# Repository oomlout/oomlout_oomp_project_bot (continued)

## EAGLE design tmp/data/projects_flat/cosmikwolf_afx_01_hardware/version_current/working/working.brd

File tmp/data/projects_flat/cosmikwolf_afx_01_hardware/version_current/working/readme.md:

# afx-01_hardware by cosmikwolf  
This is a harvested standardized copy of a project from github.  
The original project can be found at:  
https://github.com/cosmikwolf/afx-01_hardware  
Please consult that link for additional, details, files, and license information.  
Note: It was auto harvested and if the original repo had more than one board file or anything out of the ordinary the files here are likely not representative.

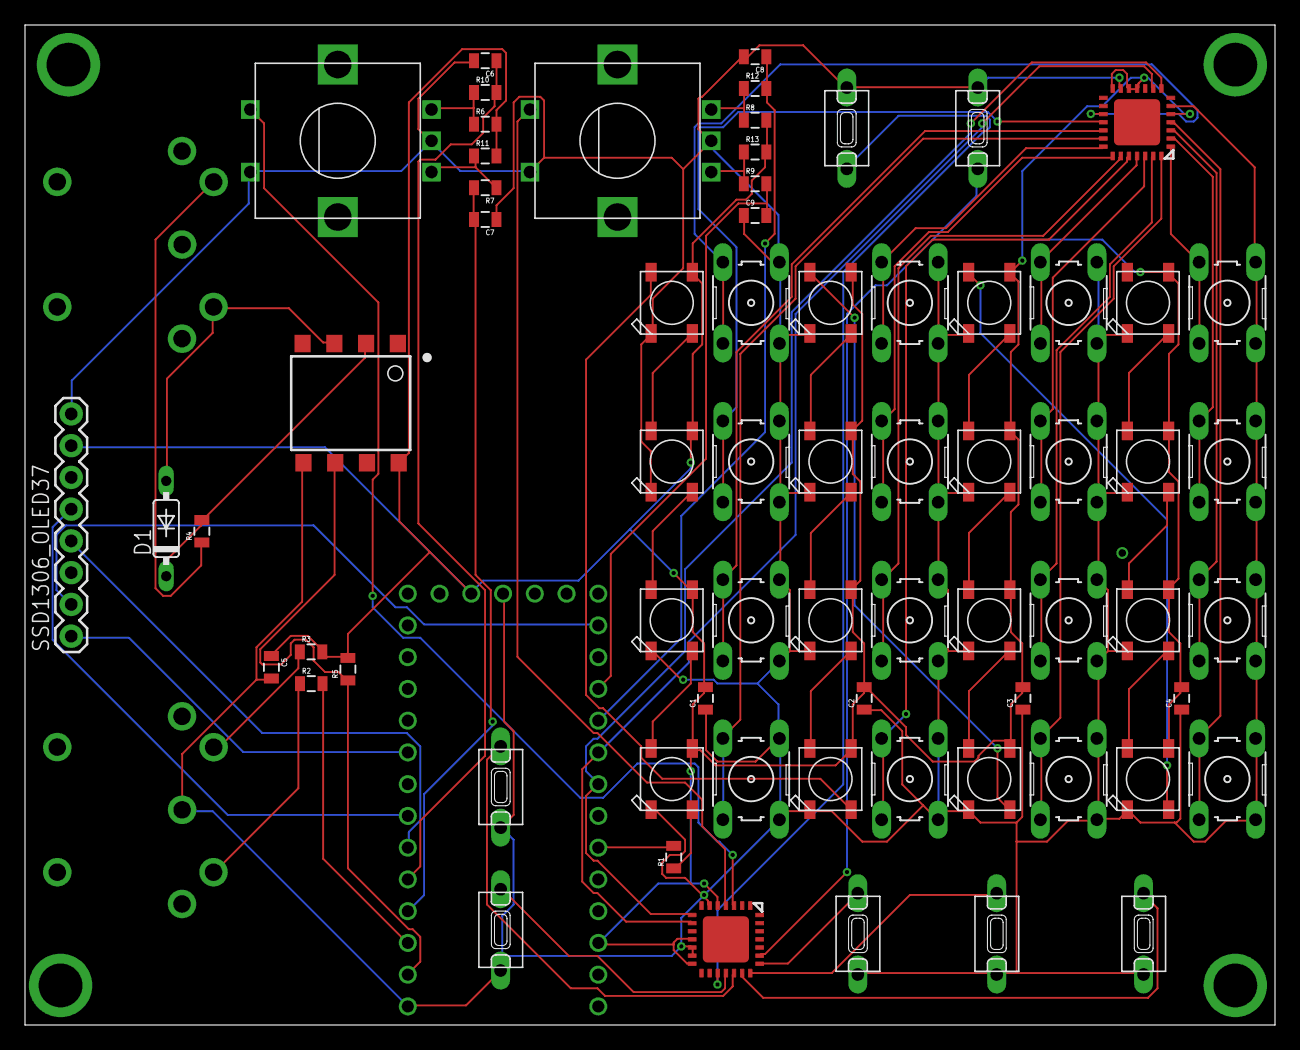
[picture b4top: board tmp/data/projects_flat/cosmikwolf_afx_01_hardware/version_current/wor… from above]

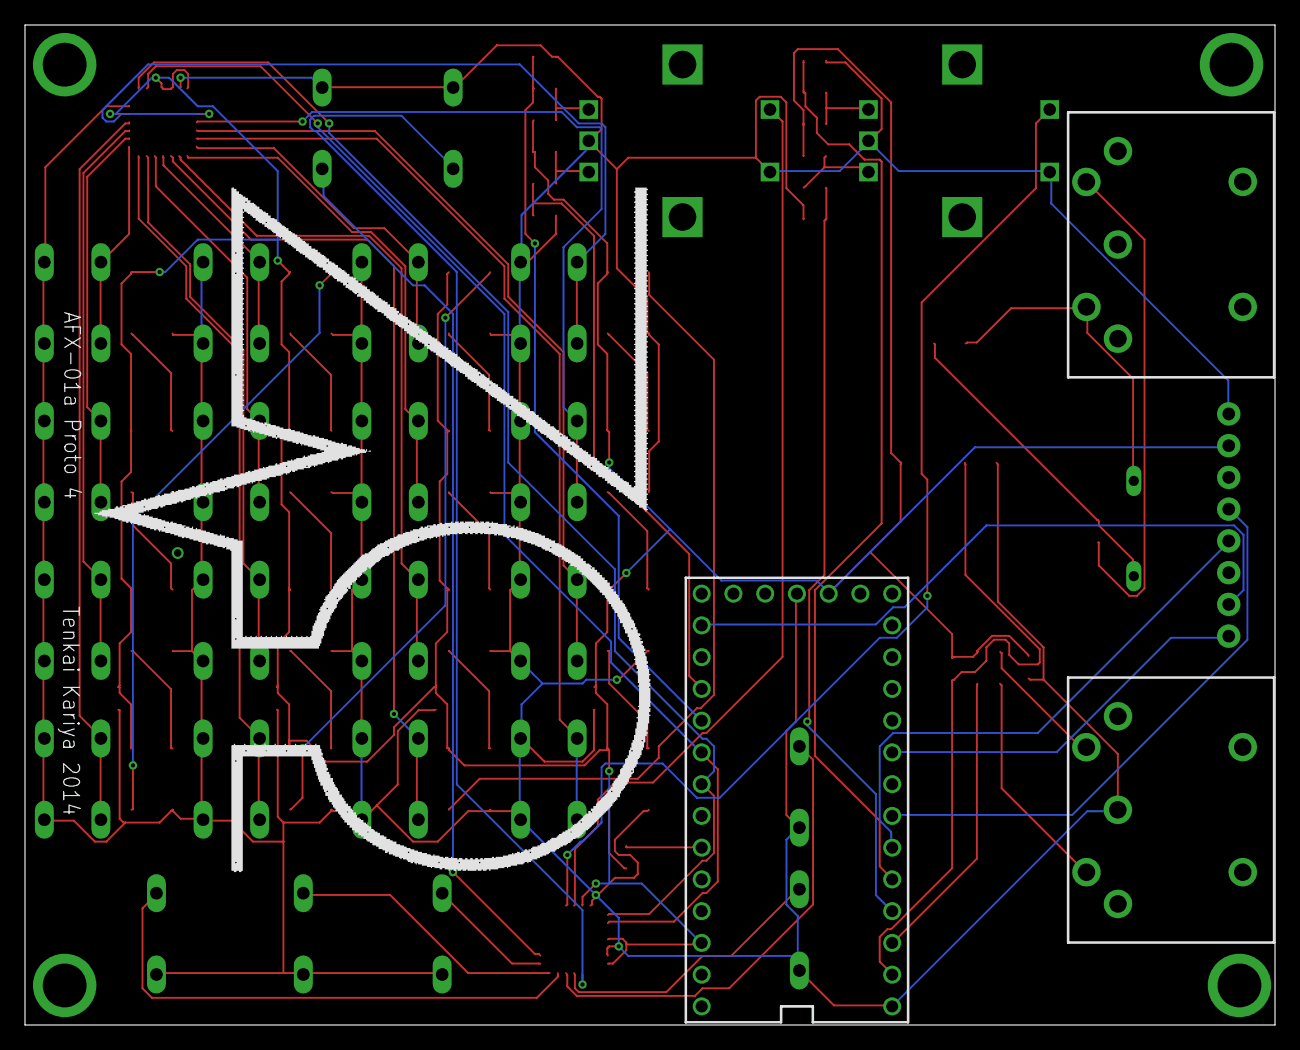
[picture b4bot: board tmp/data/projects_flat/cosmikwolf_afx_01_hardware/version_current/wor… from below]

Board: 2 copper layers, 100.0 x 80.0 mm, 71 parts (3 on the bottom side), 65 nets.

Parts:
C1, C2, C3, C4, C5: 100uF; 0805
C6, C7, C8, C9: 0.01uF; 0805
D1: 1N4148DO35-7; DO35-7
L1, L2, L3, L4, L5, L6, L7, L8, L9, L10, L11, L12, L13, L14, L15, L16: WS2812B
MCP0, MCP1: MCP23017ML; QFN28-ML_6X6MM
R1: 500; 0805
R2, R3, R4: 220; 0805
R5: 270; 0805
R6, R7, R8, R9, R10, R11, R12, R13: 10k; 0805
S1, S2, S3, S4, S5, S6, S7, S8, S9, S10, S11, S12, S13, S14, S15, S16: B3F-10XX
SS1, SS2, SS3, SS4, SS5, SS6, SS7: B3F-10XX
SSD1306_OLED37: 1X08_ROUND
SW1, SW2: EC12E_SW; ALPS_EC12E_SW
U1: 6N138M; 8-SMD
U$1: TEENSY_3.1_BASIC
U$2, U$3: MIDI_CONN_FEMALE_SUPPORT; DIN_5_FEMALE_SUPPORT

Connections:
GND: C1.1, C2.1, C3.1, C4.1, C5.2, C6.2, C7.1, C8.2, C9.1, L1.3-GND, L2.3-GND, L3.3-GND, L4.3-GND, L5.3-GND, L6.3-GND, L7.3-GND, L8.3-GND, L9.3-GND, L10.3-GND, L11.3-GND, L12.3-GND, L13.3-GND, L14.3-GND, L15.3-GND, L16.3-GND, MCP0.6, MCP0.13, MCP1.6, MCP1.12, MCP1.13, S1.3, S1.4, S2.3, S2.4, S3.3, S3.4, S4.3, S4.4, S5.3, S5.4, S6.3, S6.4, S7.3, S7.4, S8.3, S8.4, S9.3, S9.4, S10.3, S10.4, S11.3, S11.4, S12.3, S12.4, S13.3, S13.4, S14.3, S14.4, S15.3, S15.4, S16.3, S16.4, SS1.1, SS2.1, SS3.1, SS4.1, SS5.1, SS6.1, SS7.1, SSD1306_OLED37.8, SW1.C, SW1.D, SW2.C, SW2.D, U1.5, U$1.GND, U$1.GND1, U$2.2
unnamed: L1.2-DOUT, L2.4-DIN
unnamed: L2.2-DOUT, L3.4-DIN
unnamed: L3.2-DOUT, L4.4-DIN
unnamed: L5.2-DOUT, L6.4-DIN
unnamed: L6.2-DOUT, L7.4-DIN
unnamed: L7.2-DOUT, L8.4-DIN
unnamed: L9.2-DOUT, L10.4-DIN
unnamed: L10.2-DOUT, L11.4-DIN
unnamed: L11.2-DOUT, L12.4-DIN
unnamed: L13.2-DOUT, L14.4-DIN
unnamed: L14.2-DOUT, L15.4-DIN
unnamed: L15.2-DOUT, L16.4-DIN
unnamed: L4.2-DOUT, L5.4-DIN
unnamed: R2.1, U$2.5
unnamed: R2.2, U$1.1
unnamed: MCP0.20, S1.1, S1.2
unnamed: MCP0.19, S2.1, S2.2
unnamed: MCP0.18, S3.1, S3.2
unnamed: MCP0.17, S4.1, S4.2
unnamed: R1.2, U$1.21/A7
unnamed: MCP0.24, S5.1, S5.2
unnamed: MCP0.23, S6.1, S6.2
unnamed: MCP0.22, S7.1, S7.2
unnamed: MCP0.21, S8.1, S8.2
unnamed: MCP0.28, S9.1, S9.2
unnamed: MCP0.27, S10.1, S10.2
unnamed: MCP0.26, S11.1, S11.2
unnamed: MCP0.25, S12.1, S12.2
unnamed: MCP0.4, S13.1, S13.2
unnamed: MCP0.3, S14.1, S14.2
unnamed: MCP0.2, S15.1, S15.2
unnamed: MCP0.1, S16.1, S16.2
unnamed: MCP0.8, MCP1.8, U$1.19/A5
unnamed: MCP0.9, MCP1.9, U$1.18/A4
unnamed: SSD1306_OLED37.1, U$1.7
unnamed: SSD1306_OLED37.2, U$1.14/A0
unnamed: SSD1306_OLED37.4, U$1.4
unnamed: SSD1306_OLED37.5, U$1.5
unnamed: L12.2-DOUT, L13.4-DIN
unnamed: R3.1, U$2.4
unnamed: R8.1, R12.1, SW2.B
unnamed: R9.1, R13.1, SW2.A
unnamed: MCP1.4, SW2.E
unnamed: MCP1.3, SW1.E
unnamed: MCP1.17, SS7.2
unnamed: MCP1.18, SS1.2
unnamed: MCP1.19, SS2.2
unnamed: MCP1.23, SS6.2
unnamed: MCP1.22, SS5.2
unnamed: MCP1.20, SS3.2
unnamed: MCP1.21, SS4.2
unnamed: L1.4-DIN, R1.1
unnamed: L8.2-DOUT, L9.4-DIN
unnamed: R4.1, U$3.4
unnamed: D1.C, R4.2, U1.2
unnamed: D1.A, U1.3, U$3.5
unnamed: R5.1, U1.6, U$1.0
unnamed: C6.1, R10.2, U$1.3
unnamed: R6.1, R10.1, SW1.B
unnamed: R7.1, R11.1, SW1.A
unnamed: C7.2, R7.2, U$1.2
unnamed: C8.1, R12.2, U$1.17/A3
unnamed: C9.2, R9.2, U$1.16/A2
VCC: C1.2, C2.2, C3.2, C4.2, C5.1, L1.1-VDD, L2.1-VDD, L3.1-VDD, L4.1-VDD, L5.1-VDD, L6.1-VDD, L7.1-VDD, L8.1-VDD, L9.1-VDD, L10.1-VDD, L11.1-VDD, L12.1-VDD, L13.1-VDD, L14.1-VDD, L15.1-VDD, L16.1-VDD, MCP0.5, MCP0.11, MCP0.12, MCP0.14, MCP1.5, MCP1.11, MCP1.14, R3.2, R5.2, R6.2, R8.2, R11.2, R13.2, SSD1306_OLED37.7, U1.8, U$1.3.3V, U$1.3.3V1

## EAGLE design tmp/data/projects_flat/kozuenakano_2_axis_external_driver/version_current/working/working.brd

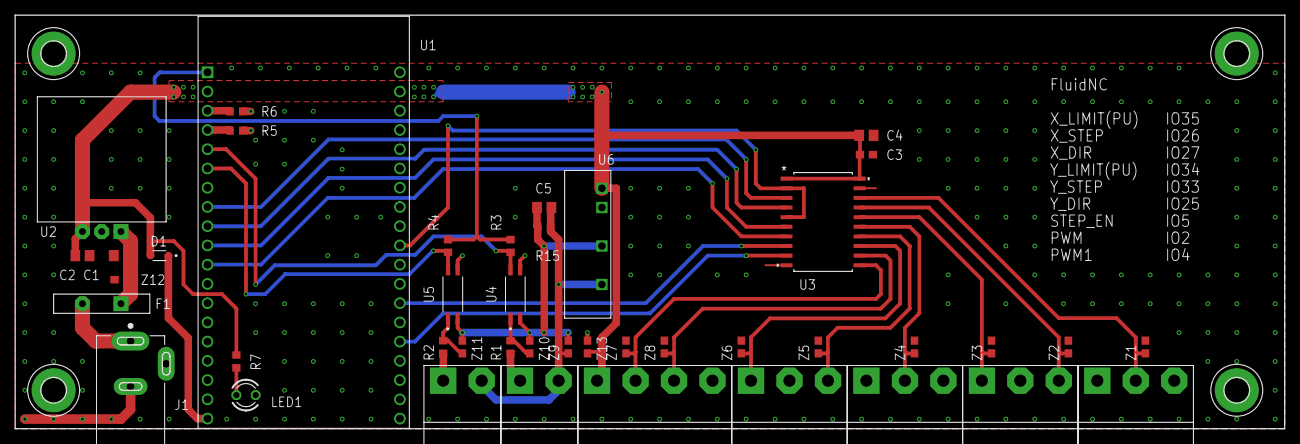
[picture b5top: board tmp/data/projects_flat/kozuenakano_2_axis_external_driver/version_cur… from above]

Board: 2 copper layers, 167.6 x 54.6 mm, 47 parts (0 on the bottom side), 32 nets.

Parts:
C1, C2, C4, C5: 10uF; C0805
C3: 0.1uF; C0603
CN1, CN2, CN3, CN4: ETB43034G000Z
CN7: ETB43044G000Z
CN8, CN9: ETB43024G000Z
D1: BAT760-7; SOD2513X120N
F1: RXE110
H1, H2, H3, H4: MOUNT-PAD-ROUND3.2; 3,2-PAD
J1: PJ-202A; CUI_PJ-202A
LED1: LED3MM
R1, R2: 220; R0603
R3, R4: 10k; R0603
R5, R6: 100k; R0603
R7: 1k; R0603
R15: 470; R0603
U1: ESP32-DEVKITC-32D; MODULE_ESP32-DEVKITC-32D
U2: BP5293-50BP5293_SIDE; BP5293_SIDE
U3: MC74ACT245DWR2G; SOIC-20WB_ONS
U4, U5: TLP291(GB-TP,SE; SOIC127P700X220-4N
U6: MAU102; MAU100_SINGLE
Z1, Z2, Z3, Z4, Z5, Z6, Z7, Z8, Z9, Z10, Z11, Z13: MLVC06V012C210; 0603
Z12: MLVC06V026C120; 0603

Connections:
+3V3: R3.2, R4.2, U1.1
+5V: C2.2, C3.1, C4.2, CN7.P$1, D1.A, R7.1, U2.P$3, U3.1, U3.20, U6.P$1, Z13.1
+12V: C1.2, F1.P$1, U2.P$1, Z12.1
GND: C1.1, C2.1, C3.2, C4.1, CN1.P$1, CN1.P$3, CN2.P$2, CN3.P$1, CN3.P$3, CN4.P$2, CN7.P$4, H1.B3,2, H2.B3,2, H3.B3,2, H4.B3,2, J1.2, J1.3, LED1.K, R5.1, R6.1, U1.14, U1.20, U1.26, U2.P$2, U3.10, U3.19, U4.3, U5.3, U6.P$2, Z1.2, Z2.2, Z3.2, Z4.2, Z5.2, Z6.2, Z7.2, Z8.2, Z12.2, Z13.2
GNDIO: C5.1, R15.1, U4.2, U5.2, U6.P$3, Z9.2, Z10.2, Z11.2
LED1_PWM_5: CN7.P$3, U3.12, Z8.1
LED_PWM_5: CN7.P$2, U3.11, Z7.1
unnamed: F1.P$2, J1.1
unnamed: D1.C, U1.19
unnamed: LED1.A, R7.2
unnamed: R1.2, U4.1, Z10.1
unnamed: R2.2, U5.1, Z11.1
unnamed: R6.2, U1.3
unnamed: R5.2, U1.4
PWM: U1.34, U3.9
PWM1: U1.32, U3.8
STEP_ENABLE: U1.29, U3.2, U3.5
STEP_EN_X_5: CN3.P$2, U3.15, Z4.1
STEP_EN_Y_5: CN1.P$2, U3.18, Z1.1
VCCIO: C5.2, CN8.P$2, CN9.P$2, R15.2, U6.P$4, Z9.1
X_DIR: U1.11, U3.7
X_DIR_5: CN4.P$1, U3.13, Z6.1
X_LIMIT: R4.1, U1.6, U5.4
X_LIMIT_IO: CN9.P$1, R2.1
X_STEP: U1.10, U3.6
X_STEP_5: CN4.P$3, U3.14, Z5.1
Y_DIR: U1.9, U3.4
Y_DIR_5: CN2.P$1, U3.16, Z3.1
Y_LIMIT: R3.1, U1.5, U4.4
Y_LIMIT_IO: CN8.P$1, R1.1
Y_STEP: U1.8, U3.3
Y_STEP_5: CN2.P$3, U3.17, Z2.1
